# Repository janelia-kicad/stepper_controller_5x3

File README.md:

- [Repository Information](#org1390894)
  - [Description](#org5e8a07c)
- [Images](#org5d62455)
- [Schematic](#org4a582db)
- [Gerbers](#org312467b)
- [Bill of Materials](#org7a5552a)
  - [PCB Parts](#orgf9d748f)
  - [Supplemental Parts](#orgd5227c2)
  - [Vendor Parts Lists](#org4a799e8)
- [Supplemental Documentation](#org5107894)
  - [Assembly Instructions](#org090c8bb)

# Repository Information

-   **Name:** stepper\_controller\_5x3
-   **Version:** 1.3
-   **License:** Open-Source Hardware
-   **URL:** <https://github.com/janelia-kicad/stepper_controller_5x3>
-   **Author:** Peter Polidoro
-   **Email:** peter@polidoro.io

## Description

This board controls up to 3 stepper motors with optional forward and reverse limit switches for each motor.

# Images

# Schematic

[./schematic/stepper\_controller\_5x3.pdf](./schematic/stepper_controller_5x3.pdf)

# Gerbers

Send gerbers zip file to your favorite PCB manufacturer for fabrication.

[./gerbers/stepper\_controller\_5x3\_v1.3.zip](./gerbers/stepper_controller_5x3_v1.3.zip)

# Bill of Materials

## PCB Parts

| Item | Reference(s)                                           | Quantity | PartNumber        | Vendor  | Description                                                               |
|---- |------------------------------------------------------ |-------- |----------------- |------- |------------------------------------------------------------------------- |
| 1    | C1 C10 C11 C14 C15 C16 C17 C20 C21 C22 C23 C4 C5 C8 C9 | 15       | 399-14636-1-ND    | digikey | CAP CER 0.1UF 50V X7R 0805                                                |
| 2    | C12 C18 C6                                             | 3        | PCE3812CT-ND      | digikey | CAP ALUM 220UF 20% 50V SMD                                                |
| 3    | C13 C19 C2 C3 C7                                       | 5        | 445-14419-1-ND    | digikey | CAP CER 10UF 35V X5R 0805                                                 |
| 4    | CLK1                                                   | 1        | CTX277LVCT-ND     | digikey | OSC XO 32.000MHZ HCMOS TTL SMD                                            |
| 5    | D1                                                     | 1        | 568-11697-1-ND    | digikey | DIODE SCHOTTKY 45V 10A CFP15                                              |
| 6    | MDB1                                                   | 2        | S1011E-25-ND      | digikey | 25 Positions Header Breakaway Connector 0.1in                             |
| 7    | P1                                                     | 1        | CP-063BH-ND       | digikey | CONN PWR JACK DC 2.5X5.5 8A T/H                                           |
| 8    | R1 R12 R2 R7                                           | 4        | P10.0KCCT-ND      | digikey | RES SMD 10K OHM 1% 1/8W 0805                                              |
| 9    | R10 R11 R13 R14 R15 R16 R3 R4 R5 R6 R8 R9              | 12       | P845CCT-ND        | digikey | RES SMD 845 OHM 1% 1/8W 0805                                              |
| 10   | REG1                                                   | 1        | 945-1395-5-ND     | digikey | CONV DC/DC 1A 5V OUT SIP VERT                                             |
| 11   | SS1 SS2 SS3                                            | 48       | ED90331-ND        | digikey | CONN PIN RCPT .025-.037 SOLDER                                            |
| 12   | T1 T3 T5                                               | 3        | 277-1152-ND       | digikey | TERM BLOCK HDR 4POS VERT 5.08MM                                           |
| 13   | T2 T4 T6                                               | 3        | 277-1223-ND       | digikey | TERM BLOCK HDR 4POS VERT 3.81MM                                           |
| 14   | U1                                                     | 1        | 1460-1071-1-ND    | digikey | IC MOTOR CONTROLLER SPI 32QFN                                             |
| 15   | U10 U2 U4 U7                                           | 4        | 296-11603-1-ND    | digikey | IC BUF NON-INVERT 5.5V SOT23-5                                            |
| 16   | U11 U5 U8                                              | 3        | MAX6817EUT+TCT-ND | digikey | IC DEBOUNCER SWITCH DUAL SOT23-6                                          |
| 17   | U12 U6 U9                                              | 3        | 516-2614-1-ND     | digikey | OPTOISO 3.75KV 2CH PUSH PULL 8SO                                          |
| 18   | U3                                                     | 1        | 296-14668-1-ND    | digikey | Buffer Non-Inverting 1 Element 8 Bit per Element Push-Pull Output 20-SOIC |

## Supplemental Parts

| Item | Quantity | PartNumber       | Vendor  | Description                       |
|---- |-------- |---------------- |------- |--------------------------------- |
| 1    | 3        | 277-1013-ND      | digikey | TERM BLOCK PLUG 4POS STR 5.08MM   |
| 2    | 3        | 277-1042-ND      | digikey | TERM BLOCK PLUG 4POS 5.08MM       |
| 3    | 3        | 277-1163-ND      | digikey | TERM BLOCK PLUG 4POS STR 3.81MM   |
| 4    | 3        | 277-1193-ND      | digikey | TERM BLOCK PLUG 4POS 90DEG 3.81MM |
| 5    | 3        | 1460-1187-ND     | digikey | TMC2130 STEPPER DRIVER BOARD      |
| 6    | 3        | 501100B00000G-ND | digikey | HEATSINK 14-DIP/16-DIP            |
| 7    | 1        | 3M10315-ND       | digikey | TAPE ADHESIVE TRANSFER 1/2in X5YD |

## Vendor Parts Lists

[./bom/digikey\_parts.csv](./bom/digikey_parts.csv)

[./bom/supplemental\_digikey\_parts.csv](./bom/supplemental_digikey_parts.csv)

# Supplemental Documentation

## Assembly Instructions

-   Solder header pins into the stepper driver board(s), making note of TOP label. Insert header pins on bottom of board so that the long unsoldered header pins point down when the TOP label faces up.
-   Expose one side of the thermal adhesive tape and attach to the bottom of the heatsink. Trim tape so it does not extend beyond heatsink edges.
-   Expose the other side of the thermal adhesive tape and attach the heatsink to the stepper driver board on the side with the TOP label.
-   Solder surface mount and through hole components onto the pcb.
-   Insert stepper driver board(s) into pin receptacles.

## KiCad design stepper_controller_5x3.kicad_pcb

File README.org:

# Created 2019-04-11 Thu 14:58
#+OPTIONS: title:nil author:nil email:nil toc:t |:t ^:nil
* Repository Information

- Name :: stepper_controller_5x3
- Version :: 1.3
- License :: Open-Source Hardware
- URL :: https://github.com/janelia-kicad/stepper_controller_5x3
- Author :: Peter Polidoro
- Email :: peter@polidoro.io

** Description

This board controls up to 3 stepper motors with optional forward and reverse
limit switches for each motor.

* Images

[[file:./images/top.png]]

[[file:./images/bottom.png]]

* Schematic

[[file:./schematic/stepper_controller_5x3.pdf][./schematic/stepper_controller_5x3.pdf]]

[[file:./schematic/images/schematic00.png]]

[[file:./schematic/images/schematic01.png]]

[[file:./schematic/images/schematic02.png]]

[[file:./schematic/images/schematic03.png]]

[[file:./schematic/images/schematic04.png]]

* Gerbers

Send gerbers zip file to your favorite PCB manufacturer for fabrication.

[[file:./gerbers/stepper_controller_5x3_v1.3.zip][./gerbers/stepper_controller_5x3_v1.3.zip]]

[[file:./gerbers/images/gerbers00.png]]

[[file:./gerbers/images/gerbers01.png]]

* Bill of Materials

** PCB Parts

| Item | Reference(s)                                           | Quantity | PartNumber        | Vendor  | Description                                                               |
|------+--------------------------------------------------------+----------+-------------------+---------+---------------------------------------------------------------------------|
|    1 | C1 C10 C11 C14 C15 C16 C17 C20 C21 C22 C23 C4 C5 C8 C9 |       15 | 399-14636-1-ND    | digikey | CAP CER 0.1UF 50V X7R 0805                                                |
|    2 | C12 C18 C6                                             |        3 | PCE3812CT-ND      | digikey | CAP ALUM 220UF 20% 50V SMD                                                |
|    3 | C13 C19 C2 C3 C7                                       |        5 | 445-14419-1-ND    | digikey | CAP CER 10UF 35V X5R 0805                                                 |
|    4 | CLK1                                                   |        1 | CTX277LVCT-ND     | digikey | OSC XO 32.000MHZ HCMOS TTL SMD                                            |
|    5 | D1                                                     |        1 | 568-11697-1-ND    | digikey | DIODE SCHOTTKY 45V 10A CFP15                                              |
|    6 | MDB1                                                   |        2 | S1011E-25-ND      | digikey | 25 Positions Header Breakaway Connector 0.1in                             |
|    7 | P1                                                     |        1 | CP-063BH-ND       | digikey | CONN PWR JACK DC 2.5X5.5 8A T/H                                           |
|    8 | R1 R12 R2 R7                                           |        4 | P10.0KCCT-ND      | digikey | RES SMD 10K OHM 1% 1/8W 0805                                              |
|    9 | R10 R11 R13 R14 R15 R16 R3 R4 R5 R6 R8 R9              |       12 | P845CCT-ND        | digikey | RES SMD 845 OHM 1% 1/8W 0805                                              |
|   10 | REG1                                                   |        1 | 945-1395-5-ND     | digikey | CONV DC/DC 1A 5V OUT SIP VERT                                             |
|   11 | SS1 SS2 SS3                                            |       48 | ED90331-ND        | digikey | CONN PIN RCPT .025-.037 SOLDER                                            |
|   12 | T1 T3 T5                                               |        3 | 277-1152-ND       | digikey | TERM BLOCK HDR 4POS VERT 5.08MM                                           |
|   13 | T2 T4 T6                                               |        3 | 277-1223-ND       | digikey | TERM BLOCK HDR 4POS VERT 3.81MM                                           |
|   14 | U1                                                     |        1 | 1460-1071-1-ND    | digikey | IC MOTOR CONTROLLER SPI 32QFN                                             |
|   15 | U10 U2 U4 U7                                           |        4 | 296-11603-1-ND    | digikey | IC BUF NON-INVERT 5.5V SOT23-5                                            |
|   16 | U11 U5 U8                                              |        3 | MAX6817EUT+TCT-ND | digikey | IC DEBOUNCER SWITCH DUAL SOT23-6                                          |
|   17 | U12 U6 U9                                              |        3 | 516-2614-1-ND     | digikey | OPTOISO 3.75KV 2CH PUSH PULL 8SO                                          |
|   18 | U3                                                     |        1 | 296-14668-1-ND    | digikey | Buffer Non-Inverting 1 Element 8 Bit per Element Push-Pull Output 20-SOIC |

** Supplemental Parts

| Item | Quantity | PartNumber       | Vendor  | Description                       |
|------+----------+------------------+---------+-----------------------------------|
|    1 |        3 | 277-1013-ND      | digikey | TERM BLOCK PLUG 4POS STR 5.08MM   |
|    2 |        3 | 277-1042-ND      | digikey | TERM BLOCK PLUG 4POS 5.08MM       |
|    3 |        3 | 277-1163-ND      | digikey | TERM BLOCK PLUG 4POS STR 3.81MM   |
|    4 |        3 | 277-1193-ND      | digikey | TERM BLOCK PLUG 4POS 90DEG 3.81MM |
|    5 |        3 | 1460-1187-ND     | digikey | TMC2130 STEPPER DRIVER BOARD      |
|    6 |        3 | 501100B00000G-ND | digikey | HEATSINK 14-DIP/16-DIP            |
|    7 |        1 | 3M10315-ND       | digikey | TAPE ADHESIVE TRANSFER 1/2in X5YD |

** Vendor Parts Lists

[[file:./bom/digikey_parts.csv][./bom/digikey_parts.csv]]

[[file:./bom/supplemental_digikey_parts.csv][./bom/supplemental_digikey_parts.csv]]

* Supplemental Documentation

** Assembly Instructions

- Solder header pins into the stepper driver board(s), making note of TOP label.
  Insert header pins on bottom of board so that the long unsoldered header
  pins point down when the TOP label faces up.
- Expose one side of the thermal adhesive tape and attach to the bottom of the
  heatsink. Trim tape so it does not extend beyond heatsink edges.
- Expose the other side of the thermal adhesive tape and attach the heatsink
  to the stepper driver board on the side with the TOP label.
- Solder surface mount and through hole components onto the pcb.
- Insert stepper driver board(s) into pin receptacles.

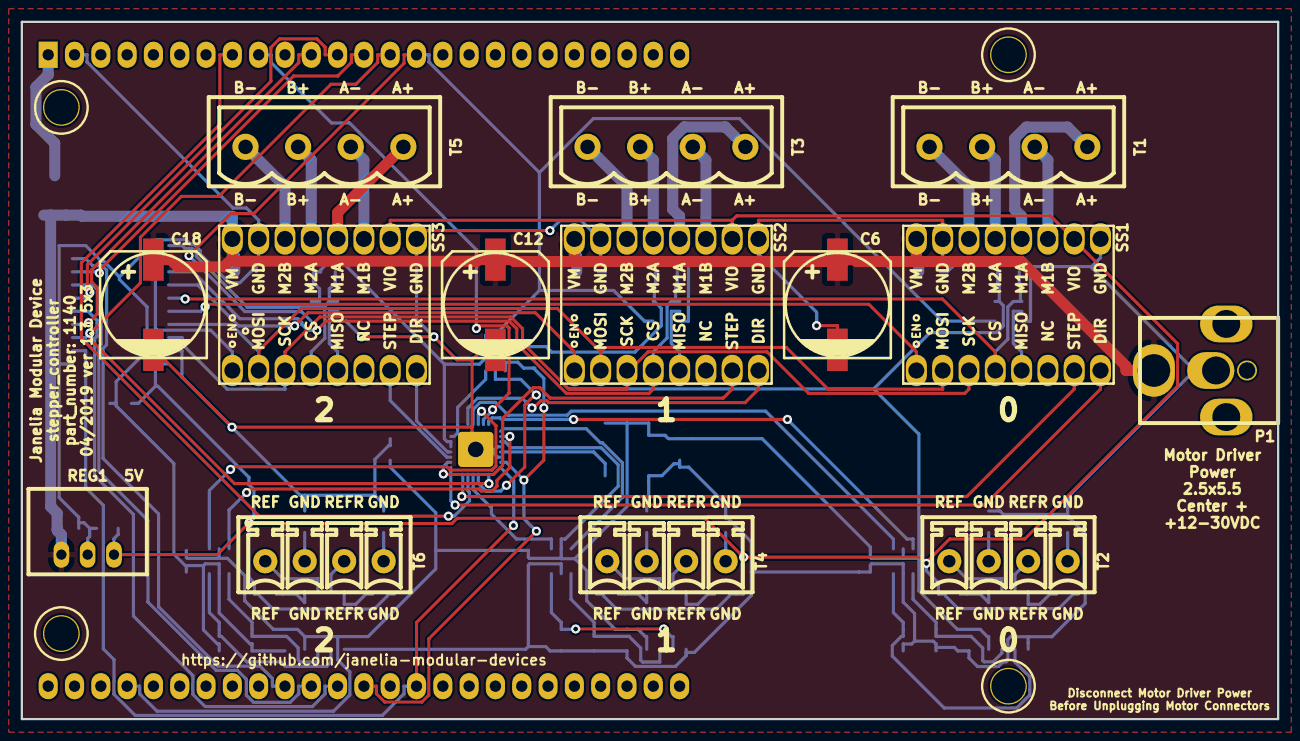
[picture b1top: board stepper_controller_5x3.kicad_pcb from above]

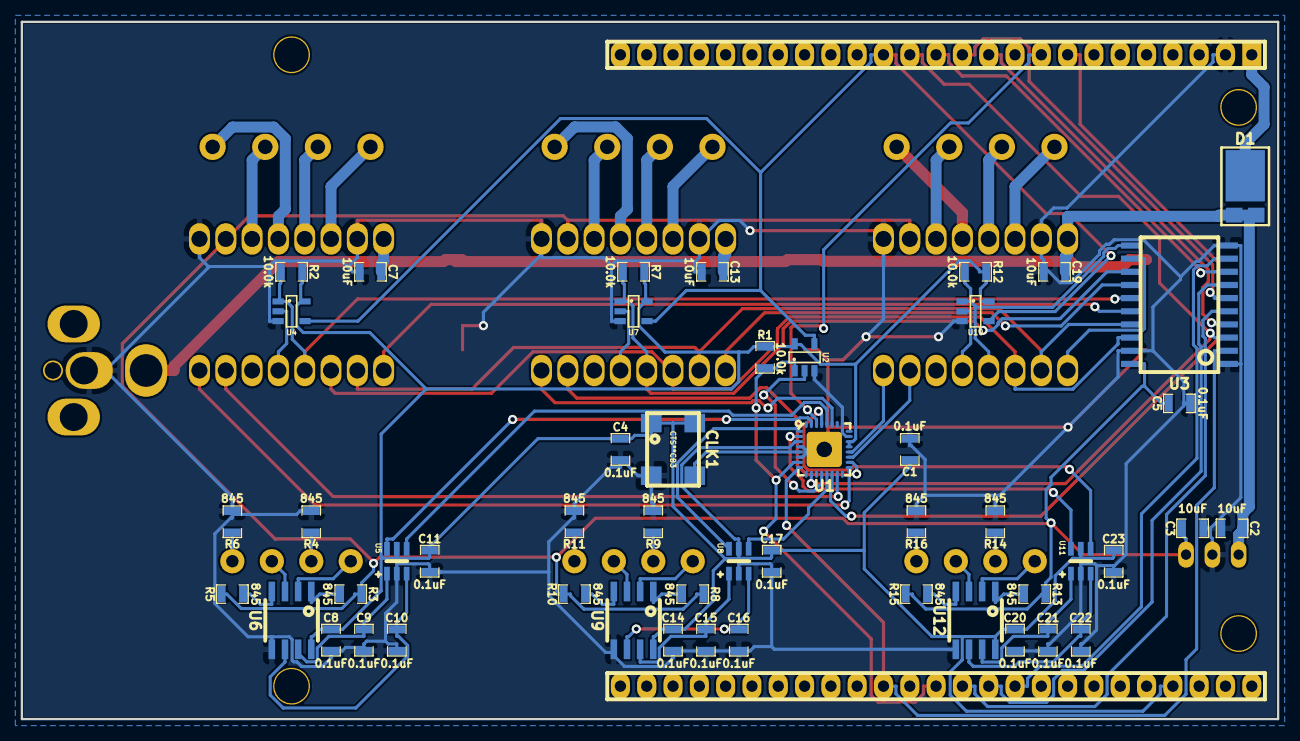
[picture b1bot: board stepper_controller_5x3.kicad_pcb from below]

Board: 2 copper layers, 121.3 x 67.3 mm, 65 parts (50 on the bottom side), 78 nets.

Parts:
C1, C4, C5, C8, C9, C10, C11, C14, C15, C16, C17, C20, C21, C22, C23: 0.1uF; SM0805
C2, C3, C7, C13, C19: 10uF; SM0805
C6, C12, C18: 220uF_POL; C_ELEC_10
CLK1: CLK_32MHZ; CTS_SMD_4_7X5MM
D1: diode_schottky_45V_10A; CFP15
MDB1: MODULAR_DEVICE_BASE_5x3_MALE; MODULAR_DEVICE_BASE_5X3_MALE
P1: PWR_JACK_2.5x5.5; DCJACK_2PIN_HIGHCURRENT
R1, R2, R7, R12: 10.0k; SM0805
R3, R4, R5, R6, R8, R9, R10, R11, R13, R14, R15, R16: 845; SM0805
REG1: CONV_DC_DC_5V_1A; DC_DC_CONV_R78C
SS1, SS2, SS3: STEPSTICK
T1, T3, T5: TERM_BLK_HDR_4POS_VERT_0.2IN
T2, T4, T6: TERM_BLK_HDR_4POS_VERT_0.150IN
U1: TMC429; QFN-5x5-32
U2, U4, U7, U10: BUFFER_TRI_STATE; SOT-23-5
U3: SN74ABT541BDWR; SOIC_20
U5, U8, U11: MAX6817
U6, U9, U12: OPTOISO_2CHAN; SO-8

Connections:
+3V3: C1.1, C4.1, C8.1, C11.1, C14.1, C17.1, C20.1, C23.1, CLK1.1, CLK1.4, MDB1.3V3, R1.1, R2.1, R7.1, R12.1, U1.3, U1.21, U1.22, U2.5, U4.5, U5.5, U6.8, U7.5, U8.5, U9.8, U10.5, U11.5, U12.8
+5V: C3.1, C5.1, R3.1, R5.1, R8.1, R10.1, R13.1, R15.1, REG1.3, SS1.15, SS2.15, SS3.15, U3.20
/CLK: CLK1.3, U1.5
/CS_429: MDB1.15, R1.2, U1.7, U2.1
/CS_DRIVER_0: MDB1.16, U3.5
/CS_DRIVER_1: MDB1.17, U3.7
/CS_DRIVER_2: MDB1.18, U3.9
/ENABLE_0: MDB1.40, U3.4
/ENABLE_1: MDB1.41, U3.6
/ENABLE_2: MDB1.42, U3.8
/INT: MDB1.5, U1.14
/MISO: MDB1.12, U2.4, U4.4, U7.4, U10.4
/MOSI: MDB1.11, U1.10, U3.3
/POSCOMP: MDB1.6, U1.30
/SCK: MDB1.13, U1.8, U3.2
/tmc429_driver_0/DIR_0: SS1.1, U1.17
/tmc429_driver_0/DIR_1: SS2.1, U1.27
/tmc429_driver_0/DIR_2: SS3.1, U1.20
/tmc429_driver_0/MISO_UB: U1.12, U2.2
/tmc429_driver_0/MOSI_B: SS1.7, SS2.7, SS3.7, U3.17
/tmc429_driver_0/REFR_0: U1.28, U5.4
/tmc429_driver_0/REFR_1: U1.13, U8.4
/tmc429_driver_0/REFR_2: U1.29, U11.4
/tmc429_driver_0/REF_0: U1.31, U5.6
/tmc429_driver_0/REF_1: U1.1, U8.6
/tmc429_driver_0/REF_2: U1.2, U11.6
/tmc429_driver_0/SCK_B: SS1.6, SS2.6, SS3.6, U3.18
/tmc429_driver_0/STEP_0: SS1.2, U1.15
/tmc429_driver_0/STEP_1: SS2.2, U1.18
/tmc429_driver_0/STEP_2: SS3.2, U1.19
/tmc429_driver_0/stepper_0/A_+: SS1.13, T1.4
/tmc429_driver_0/stepper_0/A_-: SS1.14, T1.3
/tmc429_driver_0/stepper_0/B_+: SS1.12, T1.2
/tmc429_driver_0/stepper_0/B_-: SS1.11, T1.1
/tmc429_driver_0/stepper_0/MISO_UB: SS1.4, U4.2
/tmc429_driver_0/stepper_0/REFR_B: T2.3, U6.3
/tmc429_driver_0/stepper_0/REFR_BI: C10.1, U5.3, U6.6
/tmc429_driver_0/stepper_0/REFR_GND: R6.1, T2.4
/tmc429_driver_0/stepper_0/REFR_PWR: R5.2, U6.4
/tmc429_driver_0/stepper_0/REF_B: T2.1, U6.2
/tmc429_driver_0/stepper_0/REF_BI: C9.1, U5.1, U6.7
/tmc429_driver_0/stepper_0/REF_GND: R4.1, T2.2
/tmc429_driver_0/stepper_0/REF_PWR: R3.2, U6.1
/tmc429_driver_0/stepper_1/A_+: SS2.13, T3.4
/tmc429_driver_0/stepper_1/A_-: SS2.14, T3.3
/tmc429_driver_0/stepper_1/B_+: SS2.12, T3.2
/tmc429_driver_0/stepper_1/B_-: SS2.11, T3.1
/tmc429_driver_0/stepper_1/MISO_UB: SS2.4, U7.2
/tmc429_driver_0/stepper_1/REFR_B: T4.3, U9.3
/tmc429_driver_0/stepper_1/REFR_BI: C16.1, U8.3, U9.6
/tmc429_driver_0/stepper_1/REFR_GND: R11.1, T4.4
/tmc429_driver_0/stepper_1/REFR_PWR: R10.2, U9.4
/tmc429_driver_0/stepper_1/REF_B: T4.1, U9.2
/tmc429_driver_0/stepper_1/REF_BI: C15.1, U8.1, U9.7
/tmc429_driver_0/stepper_1/REF_GND: R9.1, T4.2
/tmc429_driver_0/stepper_1/REF_PWR: R8.2, U9.1
/tmc429_driver_0/stepper_2/A_+: SS3.13, T5.4
/tmc429_driver_0/stepper_2/A_-: SS3.14, T5.3
/tmc429_driver_0/stepper_2/B_+: SS3.12, T5.2
/tmc429_driver_0/stepper_2/B_-: SS3.11, T5.1
/tmc429_driver_0/stepper_2/MISO_UB: SS3.4, U10.2
/tmc429_driver_0/stepper_2/REFR_B: T6.3, U12.3
/tmc429_driver_0/stepper_2/REFR_BI: C22.1, U11.3, U12.6
/tmc429_driver_0/stepper_2/REFR_GND: R16.1, T6.4
/tmc429_driver_0/stepper_2/REFR_PWR: R15.2, U12.4
/tmc429_driver_0/stepper_2/REF_B: T6.1, U12.2
/tmc429_driver_0/stepper_2/REF_BI: C21.1, U11.1, U12.7
/tmc429_driver_0/stepper_2/REF_GND: R14.1, T6.2
/tmc429_driver_0/stepper_2/REF_PWR: R13.2, U12.1
/tmc429_driver_0/~CS_DRIVER_0_B: R2.2, SS1.5, U3.15, U4.1
/tmc429_driver_0/~CS_DRIVER_1_B: R7.2, SS2.5, U3.13, U7.1
/tmc429_driver_0/~CS_DRIVER_2_B: R12.2, SS3.5, U3.11, U10.1
/tmc429_driver_0/~ENABLE_0_B: SS1.8, U3.16
/tmc429_driver_0/~ENABLE_1_B: SS2.8, U3.14
/tmc429_driver_0/~ENABLE_2_B: SS3.8, U3.12
GND: C1.2, C2.2, C3.2, C4.2, C5.2, C6.2, C7.2, C8.2, C9.2, C10.2, C11.2, C12.2, C13.2, C14.2, C15.2, C16.2, C17.2, C18.2, C19.2, C20.2, C21.2, C22.2, C23.2, CLK1.2, MDB1.GND, P1.2, R4.2, R6.2, R9.2, R11.2, R14.2, R16.2, REG1.2, SS1.10, SS1.16, SS2.10, SS2.16, SS3.10, SS3.16, U1.4, U1.6, U1.23, U1.25, U1.PAD, U2.3, U3.1, U3.10, U3.19, U4.3, U5.2, U6.5, U7.3, U8.2, U9.5, U10.3, U11.2, U12.5
VAA: C2.1, C6.1, C7.1, C12.1, C13.1, C18.1, C19.1, D1.2, P1.1, REG1.1, SS1.9, SS2.9, SS3.9
VDD: D1.1, MDB1.VDD

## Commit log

2017-03-31 Initial commit.
2017-03-31 Added files from stepper_controller_3x2.
2017-03-31 Made some changes.
2017-03-31 Made changes.
2017-06-15 tmc26x -> driver.
2017-06-15 Resized component.
2017-06-16 Progress towards v1.0.
2017-06-19 Finished v1.0.
2017-09-13 Updated 0.1uF capacitors.
2017-09-22 Removed extra libraries.
2017-10-23 Progress toward v1.1.
2017-10-24 More progress towards v1.1.
2017-10-25 Finished version 1.1.
2018-01-08 Updated to v4.
2018-01-08 Added v4 files.
2018-01-08 Updated gitignore.
2018-03-09 Update license from software to hardware.
2018-04-12 README.md -> README.org.
2018-04-19 Added .DS_Store to .gitignore.
2018-05-16 Added images.
2018-05-16 Added generate_kicad_documentation submodule.
2018-05-16 Preparing documentation.
2018-05-17 Updated submodules.
2018-05-17 Updated images.
2018-05-17 Updated documentation.
2018-05-18 Updated README.
2018-08-12 Marked extra Teensy 3.5 Pins.
2018-08-12 Removed v4 files.
2018-08-24 Removed F.SilkS from pads.
2018-08-27 Removed *.SilkS from pads.
2018-11-02 Added README.md.
2019-03-25 Changes towards v1.2
2019-03-28 More progress towards v1.2
2019-04-01 Test routing of new version
2019-04-02 Update documentation
2019-04-02 Remove superfluous file
2019-04-11 Add limit switch filter capacitors
2019-04-11 Fixed broken schematic.
2019-04-11 footprints: -> stepper_controller_5x3:
2021-09-16 Update email address
2021-09-21 Remove ignored files
2022-02-22 Add guix files
2022-02-23 Add guix documentation
